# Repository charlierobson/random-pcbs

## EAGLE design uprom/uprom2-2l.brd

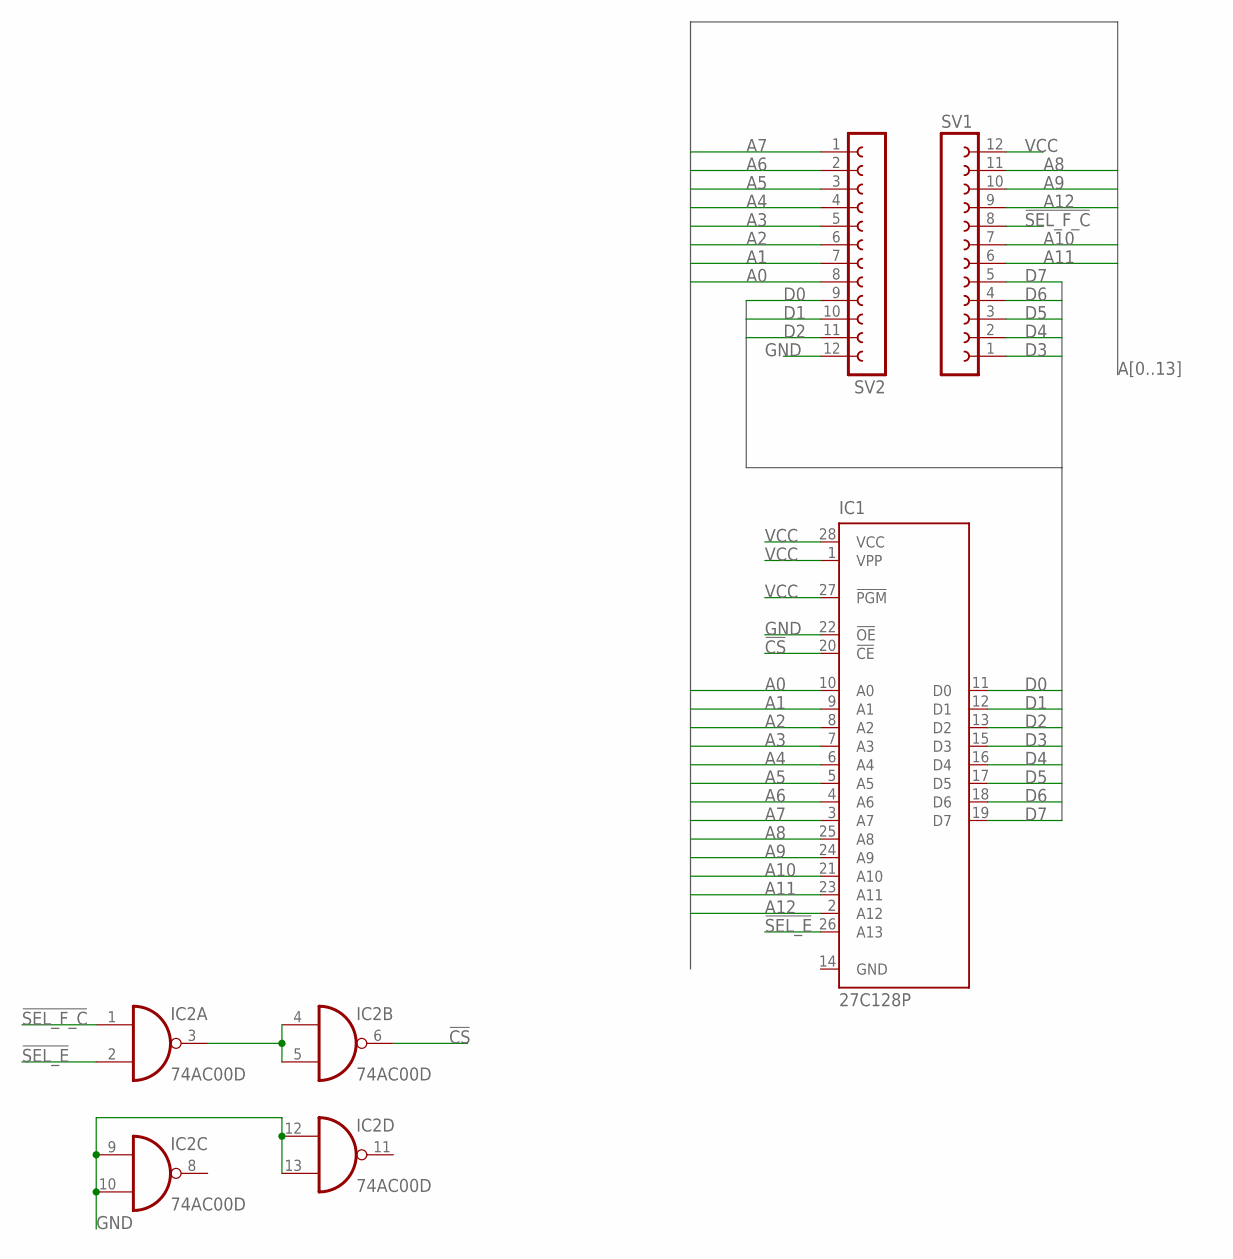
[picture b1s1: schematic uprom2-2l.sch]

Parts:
IC1: 27C128P; DIL28-6
IC2: 74AC00D; SO14
SV1, SV2: FE12-1; FE12

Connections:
!CS: IC1.20 (!CE), IC2.6 (O)
!SEL_E: IC1.26 (A13), IC2.2 (I1)
!SEL_F_C: IC2.1 (I0), SV1.8
A0: IC1.10 (A0), SV2.8
A1: IC1.9 (A1), SV2.7
A2: IC1.8 (A2), SV2.6
A3: IC1.7 (A3), SV2.5
A4: IC1.6 (A4), SV2.4
A5: IC1.5 (A5), SV2.3
A6: IC1.4 (A6), SV2.2
A7: IC1.3 (A7), SV2.1
A8: IC1.25 (A8), SV1.11
A9: IC1.24 (A9), SV1.10
A10: IC1.21 (A10), SV1.7
A11: IC1.23 (A11), SV1.6
A12: IC1.2 (A12), SV1.9
D0: IC1.11 (D0), SV2.9
D1: IC1.12 (D1), SV2.10
D2: IC1.13 (D2), SV2.11
D3: IC1.15 (D3), SV1.1
D4: IC1.16 (D4), SV1.2
D5: IC1.17 (D5), SV1.3
D6: IC1.18 (D6), SV1.4
D7: IC1.19 (D7), SV1.5
GND: IC1.14 (GND), IC1.22 (!OE), IC2.7 (GND), IC2.9 (I0), IC2.10 (I1), IC2.12 (I0), IC2.13 (I1), SV2.12
unnamed: IC2.3 (O), IC2.4 (I0), IC2.5 (I1)
VCC: IC1.1 (VPP), IC1.27 (!PGM), IC1.28 (VCC), IC2.14 (VCC), SV1.12

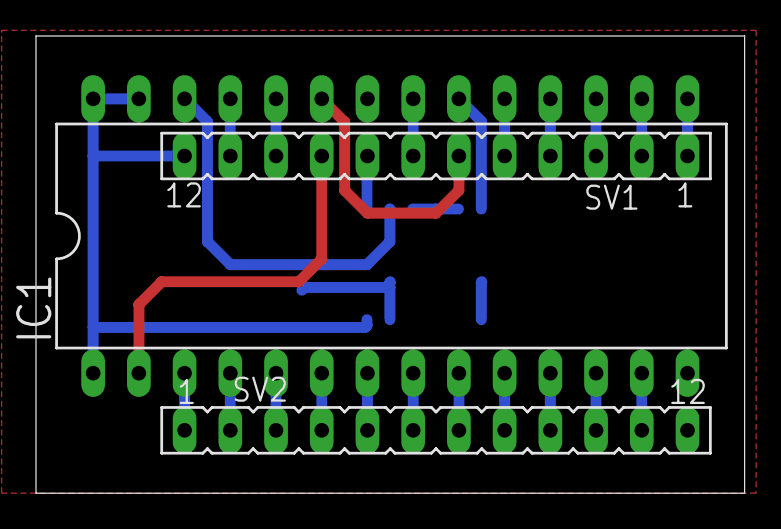
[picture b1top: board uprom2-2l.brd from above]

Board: 2 copper layers, 39.4 x 25.4 mm, 4 parts (1 on the bottom side), 27 nets.

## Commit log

2020-05-05 adding uprom
2020-05-05 compact sizr
2020-05-05 smallen
2020-05-15 uprom2
2020-05-20 final boards
